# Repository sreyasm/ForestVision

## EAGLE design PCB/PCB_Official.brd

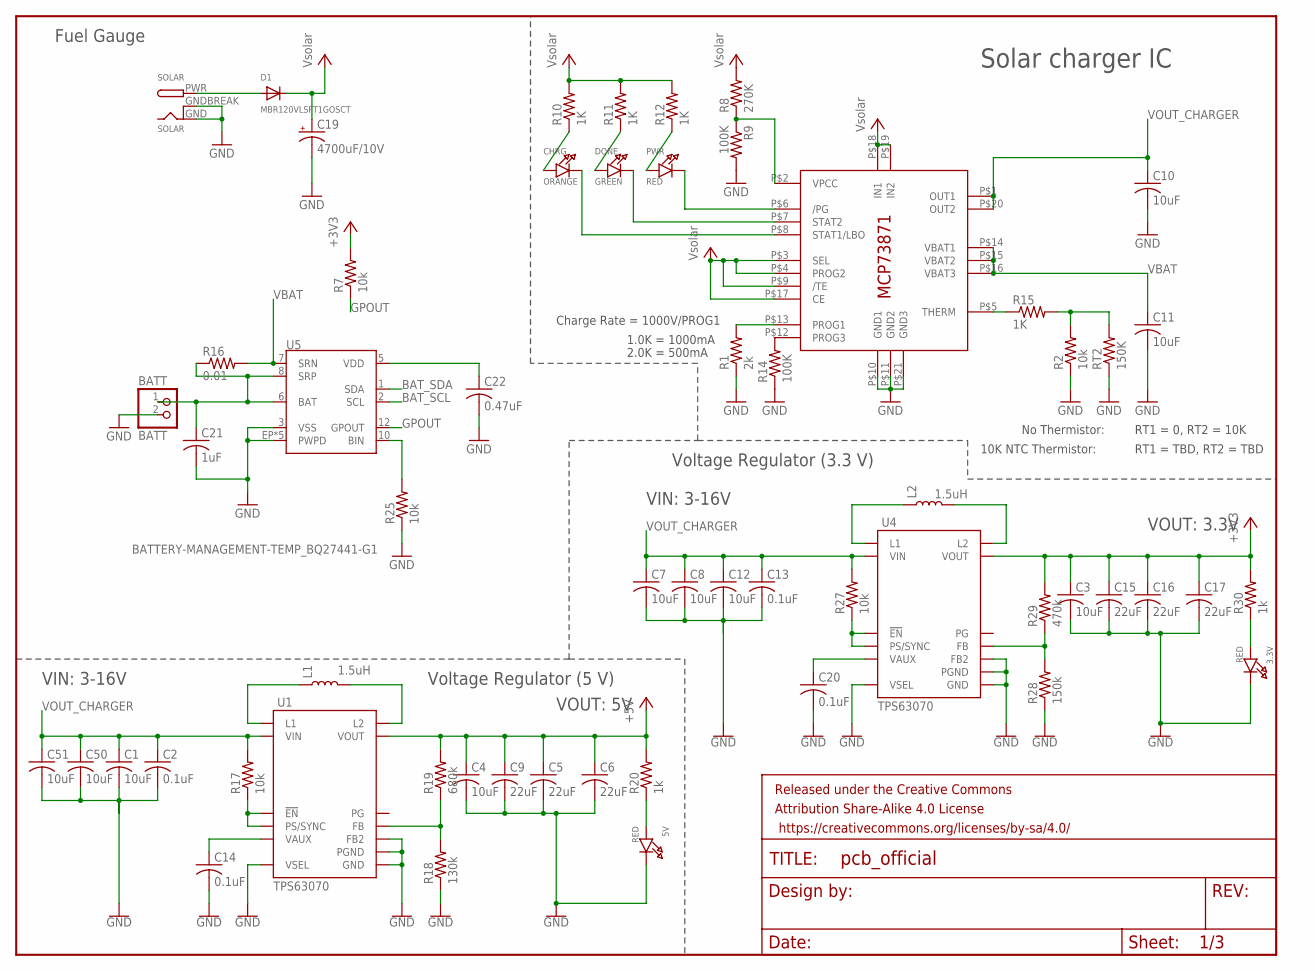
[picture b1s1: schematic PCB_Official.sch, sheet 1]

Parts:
3.3V, 5V: RED; CHIPLED_0805_NOOUTLINE
BATT: BATT; JST-PH-2-SMT-RA
C1, C8, C12, C50: 10uF; C0805
C2, C13: 0.1uF; C0805
C3, C4, C7, C51: 10uF; C0603
C5, C6, C9, C15, C16, C17: 22uF; C0805
C10, C11: 10uF; C0805K
C14, C20: 0.1uF; C0603
C19: 4700uF/10V; ADAFRUIT_E5-13
C21: 1uF; C0805
C22: 0.47uF; C0805
CHRG: ORANGE; CHIPLED_0805_NOOUTLINE
D1: MBR120VLSFT1GOSCT; MICROBUILDER_SOD-123
DONE: GREEN; CHIPLED_0805_NOOUTLINE
FRAME2: FRAME-LETTERNO_PACKAGE; DUMMY
IC1: MCP73871; QFN20_4MM
L1, L2: 1.5uH; XFL4020
PWR: RED; CHIPLED_0805_NOOUTLINE
R1: 2k; R0805
R2, R7, R25: 10k; R0805
R8: 270K; R0805
R9, R14: 100K; R0805
R10, R11, R12: 1K; R0805
R15: 1K; M0805
R16: 0.01; R0805
R17, R27: 10k; R0603
R18: 130k; R0603
R19: 680k; R0603
R20, R30: 1k; R0603
R28: 150k; R0603
R29: 470k; R0603
RT2: 150K; M0805
SOLAR: SOLAR; DCJACK_2MM_PTH
U1, U4: TPS63070; VQFN-15-HR(3X2.5)
U5: BATTERY-MANAGEMENT-TEMP_BQ27441-G1; BATTERY-MANAGEMENT-TEMP_PDSO-N12

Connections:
!EN: R17.1, U1.P$1 (PS/SYNC), U1.P$14 (!EN)
!EN1: R27.1, U4.P$1 (PS/SYNC), U4.P$14 (!EN)
+3V3: C3.1, C15.1, C16.1, C17.1, R7.2, R29.2, R30.2, U4.P$7/8 (VOUT); also elsewhere on the board
+5V: C4.1, C5.1, C6.1, C9.1, R19.2, R20.2, U1.P$7/8 (VOUT); also elsewhere on the board
BAT_SCL: U5.2 (SCL); also elsewhere on the board
BAT_SDA: U5.1 (SDA); also elsewhere on the board
GND: 3.3V.C, 5V.C, BATT.2 (1), C1.2, C2.2, C3.2, C4.2, C5.2, C6.2, C7.2, C8.2, C9.2, C10.2, C11.2, C12.2, C13.2, C14.2, C15.2, C16.2, C17.2, C19.-, C20.2, C21.2, C22.2, C50.2, C51.2, IC1.P$10 (GND1), IC1.P$11 (GND2), IC1.P$21 (GND3), R1.1, R2.1, R9.2, R14.1, R18.1, R25.1, R28.1, RT2.1, SOLAR.GND, SOLAR.GNDBREAK, U1.P$4 (GND), U1.P$6 (FB2), U1.P$10 (PGND), U1.P$15 (VSEL), U4.P$4 (GND), U4.P$6 (FB2), U4.P$10 (PGND), U4.P$15 (VSEL), U5.3 (VSS), U5.EP (PWPD), U5.EP1 (PWPD), U5.EP2 (PWPD), U5.EP3 (PWPD), U5.EP4 (PWPD); also elsewhere on the board
GPOUT: R7.1, U5.12 (GPOUT)
unnamed: L1.P$1 (1), U1.P$11 (L1)
unnamed: L1.P$2 (2), U1.P$9 (L2)
unnamed: IC1.P$2 (VPCC), R8.1, R9.1
unnamed: R18.2, R19.1, U1.P$5 (FB)
unnamed: 5V.A, R20.1
unnamed: C14.1, U1.P$3 (VAUX)
unnamed: L2.P$1 (1), U4.P$11 (L1)
unnamed: L2.P$2 (2), U4.P$9 (L2)
unnamed: C20.1, U4.P$3 (VAUX)
unnamed: IC1.P$6 (/PG), PWR.C
unnamed: DONE.C, IC1.P$7 (STAT2)
unnamed: CHRG.C, IC1.P$8 (STAT1/LBO)
unnamed: CHRG.A, R10.1
unnamed: DONE.A, R11.1
unnamed: PWR.A, R12.1
unnamed: IC1.P$12 (PROG3), R14.2
unnamed: IC1.P$13 (PROG1), R1.2
unnamed: IC1.P$5 (THERM), R15.1
unnamed: R2.2, R15.2, RT2.2
unnamed: 3.3V.A, R30.1
unnamed: R28.2, R29.1, U4.P$5 (FB)
unnamed: BATT.1 (2), C21.1, R16.1, U5.6 (BAT), U5.8 (SRP)
unnamed: C22.1, U5.5 (VDD)
unnamed: R25.2, U5.10 (BIN)
unnamed: D1.A, SOLAR.PWR
VBAT: C11.1, IC1.P$14 (VBAT1), IC1.P$15 (VBAT2), IC1.P$16 (VBAT3), R16.2, U5.7 (SRN)
VCC: C19.+, D1.C, IC1.P$3 (SEL), IC1.P$4 (PROG2), IC1.P$9 (/TE), IC1.P$17 (CE), IC1.P$18 (IN1), IC1.P$19 (IN2), R8.2, R10.2, R11.2, R12.2
VOUT_CHARGER: C1.1, C2.1, C7.1, C8.1, C10.1, C12.1, C13.1, C50.1, C51.1, IC1.P$1 (OUT1), IC1.P$20 (OUT2), R17.2, R27.2, U1.P$12/13 (VIN), U4.P$12/13 (VIN)

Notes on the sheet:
Charge Rate = 1000V/PROG1
1.0K = 1000mA
2.0K = 500mA
No Thermistor:
10K NTC Thermistor:
RT1 = 0, RT2 = 10K
RT1 = TBD, RT2 = TBD
VIN: 3-16V
VOUT: 5V
VOUT: 3.3V
Solar charger IC
Voltage Regulator (3.3 V)
Voltage Regulator (5 V)
Fuel Gauge

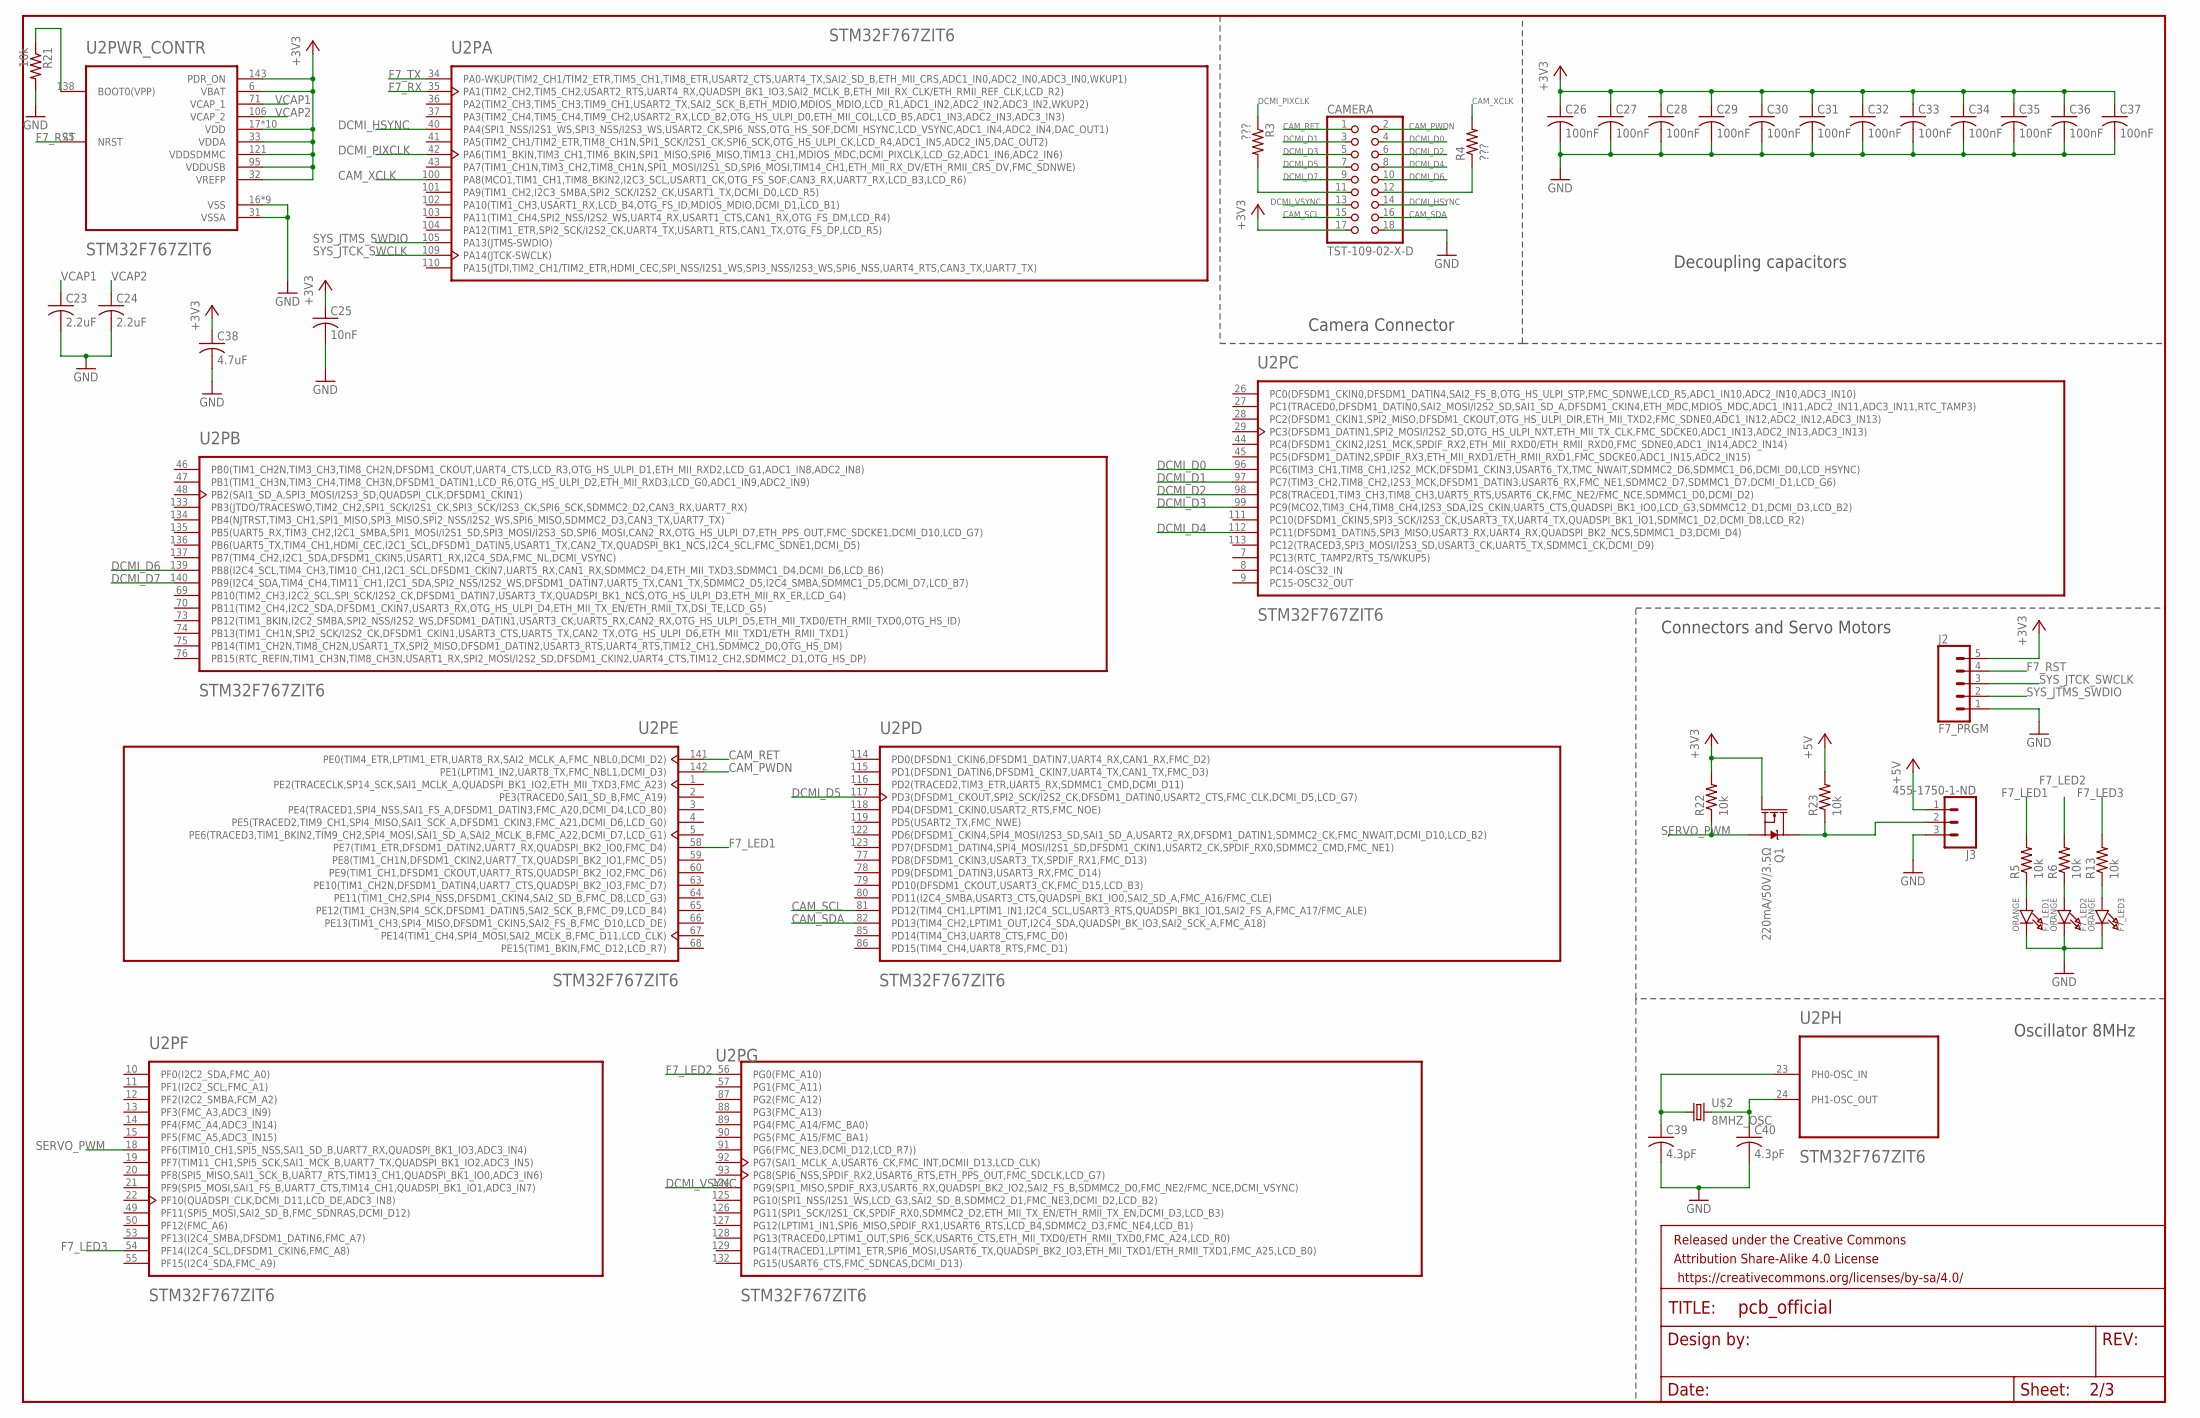
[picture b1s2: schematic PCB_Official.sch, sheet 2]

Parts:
C23, C24: 2.2uF; C0805
C25: 10nF; C0805
C26, C27, C28, C29, C30, C31, C32, C33, C34, C35, C36, C37: 100nF; C0805
C38: 4.7uF; C0805
C39, C40: 4.3pF; C0805
CAMERA: TST-109-02-X-D
F7_LED1, F7_LED2, F7_LED3: ORANGE; CHIPLED_0805_NOOUTLINE
FRAME3: FRAME-LEDGER; CREATIVE_COMMONS
J2: F7_PRGM; 1X05
J3: 455-1750-1-ND; 1X03
Q1: 220mA/50V/3.5Ω; SOT23-3
R3, R4: ???; R0805
R5, R6, R13, R21, R22, R23: 10k; R0805
U2: STM32F767ZIT6; QFP50P2200X2200X160-144N
U$2: 8MHZ_OSC

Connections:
+3V3: C25.1, C26.1, C27.1, C28.1, C29.1, C30.1, C31.1, C32.1, C33.1, C34.1, C35.1, C36.1, C37.1, C38.1, CAMERA.17, J2.5, Q1.1 (G), R22.2, U2.6 (VBAT), U2.17 (VDD), U2.30 (VDD), U2.32 (VREFP), U2.33 (VDDA), U2.39 (VDD), U2.52 (VDD), U2.62 (VDD), U2.72 (VDD), U2.84 (VDD), U2.95 (VDDUSB), U2.108 (VDD), U2.121 (VDDSDMMC), U2.131 (VDD), U2.143 (PDR_ON), U2.144 (VDD); also elsewhere on the board
+5V: J3.1, R23.2; also elsewhere on the board
CAM_PWDN: CAMERA.2, U2.142 (PE1(LPTIM1_IN2,UART8_TX,FMC_NBL1,DCMI_D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)
CAM_RET: CAMERA.1, U2.141 (PE0(TIM4_ETR,LPTIM1_ETR,UART8_RX,SAI2_M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)
CAM_SCL: CAMERA.15, U2.81 (PD12(TIM4_CH1,LPTIM1_IN1,I2C4_SCL,USART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)
CAM_SDA: CAMERA.16, U2.82 (PD13(TIM4_CH2,LPTIM1_OUT,I2C4_SDA,QUADS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)
CAM_XCLK: R4.2, U2.100 (PA8(MCO1,TIM1_CH1,TIM8_BKIN2,I2C3_SCL,U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)
DCMI_D0: CAMERA.4, U2.96 (PC6(TIM3_CH1,TIM8_CH1,I2S2_MCK,DFSDM1_C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)
DCMI_D1: CAMERA.3, U2.97 (PC7(TIM3_CH2,TIM8_CH2,I2S3_MCK,DFSDM1_D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)
DCMI_D2: CAMERA.6, U2.98 (PC8(TRACED1,TIM3_CH3,TIM8_CH3,UART5_RTS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)
DCMI_D3: CAMERA.5, U2.99 (PC9(MCO2,TIM3_CH4,TIM8_CH4,I2S3_SDA,I2S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)
DCMI_D4: CAMERA.8, U2.112 (PC11(DFSDM1_DATIN5,SPI3_MISO,USART3_RX,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)
DCMI_D5: CAMERA.7, U2.117 (PD3(DFSDM1_CKOUT,SPI2_SCK/I2S2_CK,DFSDM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)
DCMI_D6: CAMERA.10, U2.139 (PB8(I2C4_SCL,TIM4_CH3,TIM10_CH1,I2C1_SC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)
DCMI_D7: CAMERA.9, U2.140 (PB9(I2C4_SDA,TIM4_CH4,TIM11_CH1,I2C1_SD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)
DCMI_HSYNC: CAMERA.14, U2.40 (PA4(SPI1_NSS/I2S1_WS,SPI3_NSS/I2S3_WS,U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)
DCMI_PIXCLK: R3.1, U2.42 (PA6(TIM1_BKIN,TIM3_CH1,TIM6_BKIN,SPI1_M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)
DCMI_VSYNC: CAMERA.13, U2.124 (PG9(SPI1_MISO,SPDIF_RX3,USART6_RX,QUADS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)
F7_LED1: R5.2, U2.58 (PE7(TIM1_ETR,DFSDM1_DATIN2,UART7_RX,QUA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)
F7_LED2: R6.2, U2.56 (PG0(FMC_A10))
F7_LED3: R13.2, U2.54 (PF14(I2C4_SCL,DFSDM1_CKIN6,FMC_A8))
F7_RST: J2.4, U2.25 (NRST)
F7_RX: U2.35 (PA1(TIM2_CH2,TIM5_CH2,USART2_RTS,UART4_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); also elsewhere on the board
F7_TX: U2.34 (PA0-WKUP(TIM2_CH1/TIM2_ETR,TIM5_CH1,TIM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); also elsewhere on the board
GND: C23.2, C24.2, C25.2, C26.2, C27.2, C28.2, C29.2, C30.2, C31.2, C32.2, C33.2, C34.2, C35.2, C36.2, C37.2, C38.2, C39.2, C40.2, CAMERA.18, F7_LED1.C, F7_LED2.C, F7_LED3.C, J2.1, J3.3, R21.2, U2.16 (VSS), U2.31 (VSSA), U2.38 (VSS), U2.51 (VSS), U2.61 (VSS), U2.83 (VSS), U2.94 (VSS), U2.107 (VSS), U2.120 (VSS), U2.130 (VSS); also elsewhere on the board
unnamed: R21.1, U2.138 (BOOT0(VPP))
unnamed: C40.1, U2.24 (PH1-OSC_OUT), U$2.P$2 (2)
unnamed: C39.1, U2.23 (PH0-OSC_IN), U$2.P$1 (1)
unnamed: J3.2, Q1.3 (D), R23.1
unnamed: CAMERA.11, R3.2
unnamed: CAMERA.12, R4.1
unnamed: F7_LED2.A, R6.1
unnamed: F7_LED3.A, R13.1
unnamed: F7_LED1.A, R5.1
SERVO_PWM: Q1.2 (S), R22.1, U2.18 (PF6(TIM10_CH1,SPI5_NSS,SAI1_SD_B,UART7_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)
SYS_JTCK_SWCLK: J2.3, U2.109 (PA14(JTCK-SWCLK))
SYS_JTMS_SWDIO: J2.2, U2.105 (PA13(JTMS-SWDIO))
VCAP1: C23.1, U2.71 (VCAP_1)
VCAP2: C24.1, U2.106 (VCAP_2)

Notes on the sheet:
Decoupling capacitors
Camera Connector
Connectors and Servo Motors
Oscillator 8MHz

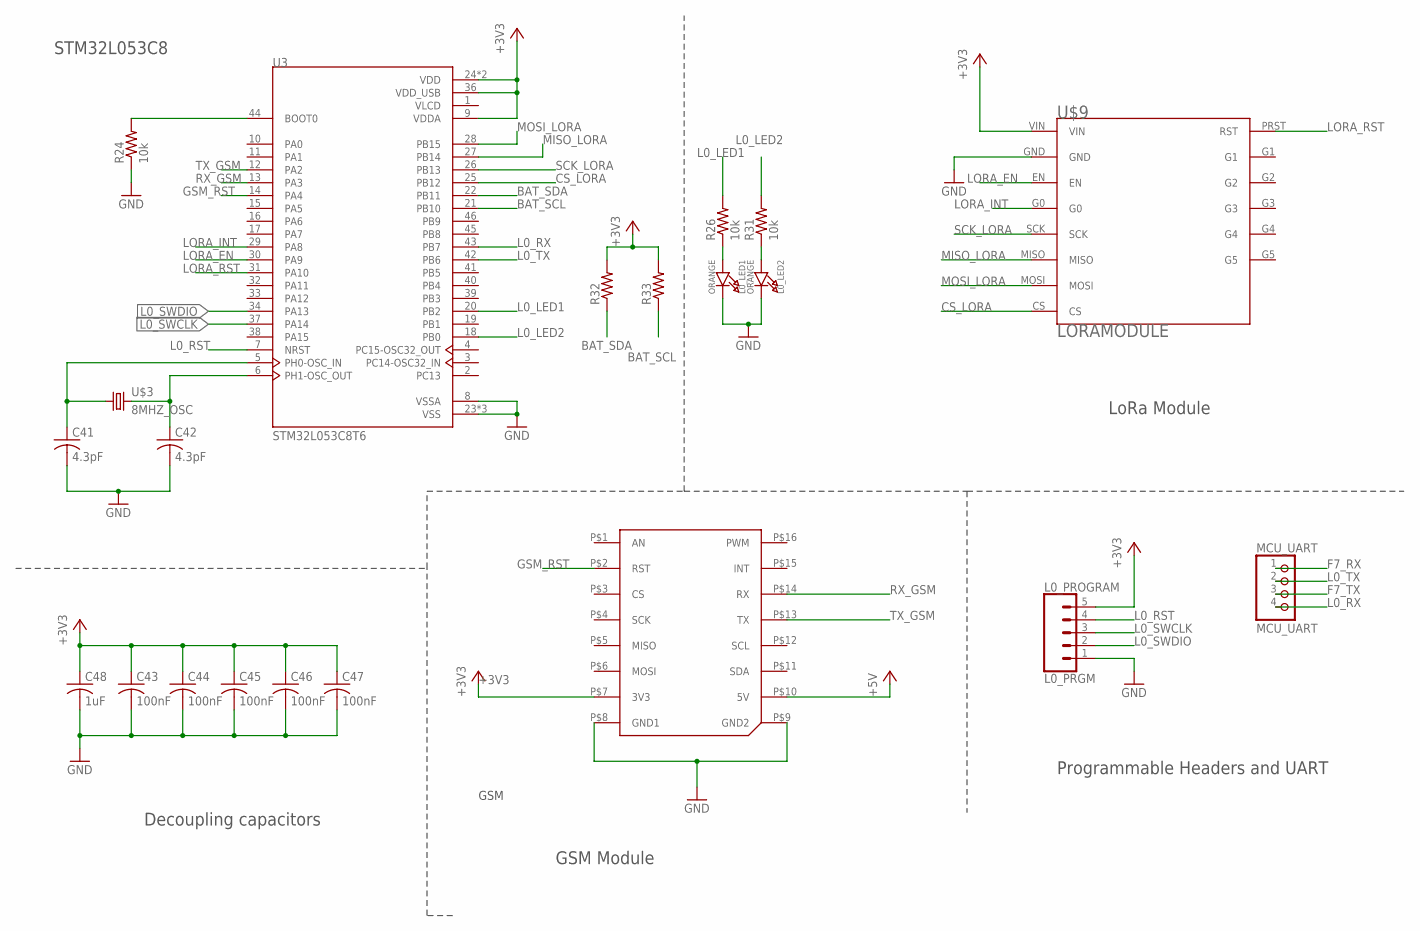
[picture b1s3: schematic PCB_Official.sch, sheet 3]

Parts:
C41, C42: 4.3pF; C0805
C43, C44, C45, C46, C47: 100nF; C0805
C48: 1uF; C0805
L0_LED1, L0_LED2: ORANGE; CHIPLED_0805_NOOUTLINE
L0_PROGRAM: L0_PRGM; 1X05
MCU_UART: MCU_UART; 1X04
R24, R26, R31: 10k; R0805
R32, R33: R-US_R0805; R0805
U3: STM32L053C8T6; QFP50P900X900X160-48N
U$1: MIKROE_CLICKLARGE; MIKROE_BUS_LARGE
U$3: 8MHZ_OSC
U$9: LORAMODULE

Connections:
+3V3: C43.1, C44.1, C45.1, C46.1, C47.1, C48.1, L0_PROGRAM.5, R32.2, R33.2, U3.9 (VDDA), U3.24 (VDD), U3.36 (VDD_USB), U3.48 (VDD), U$1.P$7 (3V3), U$9.VIN; also elsewhere on the board
+5V: U$1.P$10 (5V); also elsewhere on the board
BAT_SCL: R33.1, U3.21 (PB10); also elsewhere on the board
BAT_SDA: R32.1, U3.22 (PB11); also elsewhere on the board
CS_LORA: U3.25 (PB12), U$9.CS
F7_RX: MCU_UART.1; also elsewhere on the board
F7_TX: MCU_UART.3; also elsewhere on the board
GND: C41.2, C42.2, C43.2, C44.2, C45.2, C46.2, C47.2, C48.2, L0_LED1.C, L0_LED2.C, L0_PROGRAM.1, R24.1, U3.8 (VSSA), U3.23 (VSS), U3.35 (VSS), U3.47 (VSS), U$1.P$8 (GND1), U$1.P$9 (GND2), U$9.GND; also elsewhere on the board
GSM_RST: U3.14 (PA4), U$1.P$2 (RST)
L0_LED1: R26.2, U3.20 (PB2)
L0_LED2: R31.2, U3.18 (PB0)
L0_RST: L0_PROGRAM.4, U3.7 (NRST)
L0_RX: MCU_UART.4, U3.43 (PB7)
L0_SWCLK: L0_PROGRAM.3, U3.37 (PA14)
L0_SWDIO: L0_PROGRAM.2, U3.34 (PA13)
L0_TX: MCU_UART.2, U3.42 (PB6)
LORA_EN: U3.30 (PA9), U$9.EN
LORA_INT: U3.29 (PA8), U$9.G0
LORA_RST: U3.31 (PA10), U$9.PRST (RST)
MISO_LORA: U3.27 (PB14), U$9.MISO
MOSI_LORA: U3.28 (PB15), U$9.MOSI
unnamed: R24.2, U3.44 (BOOT0)
unnamed: C42.1, U3.6 (PH1-OSC_OUT), U$3.P$2 (2)
unnamed: C41.1, U3.5 (PH0-OSC_IN), U$3.P$1 (1)
unnamed: L0_LED2.A, R31.1
unnamed: L0_LED1.A, R26.1
RX_GSM: U3.13 (PA3), U$1.P$14 (RX)
SCK_LORA: U3.26 (PB13), U$9.SCK
TX_GSM: U3.12 (PA2), U$1.P$13 (TX)

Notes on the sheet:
GSM
Decoupling capacitors
LoRa Module
GSM Module
Programmable Headers and UART
STM32L053C8

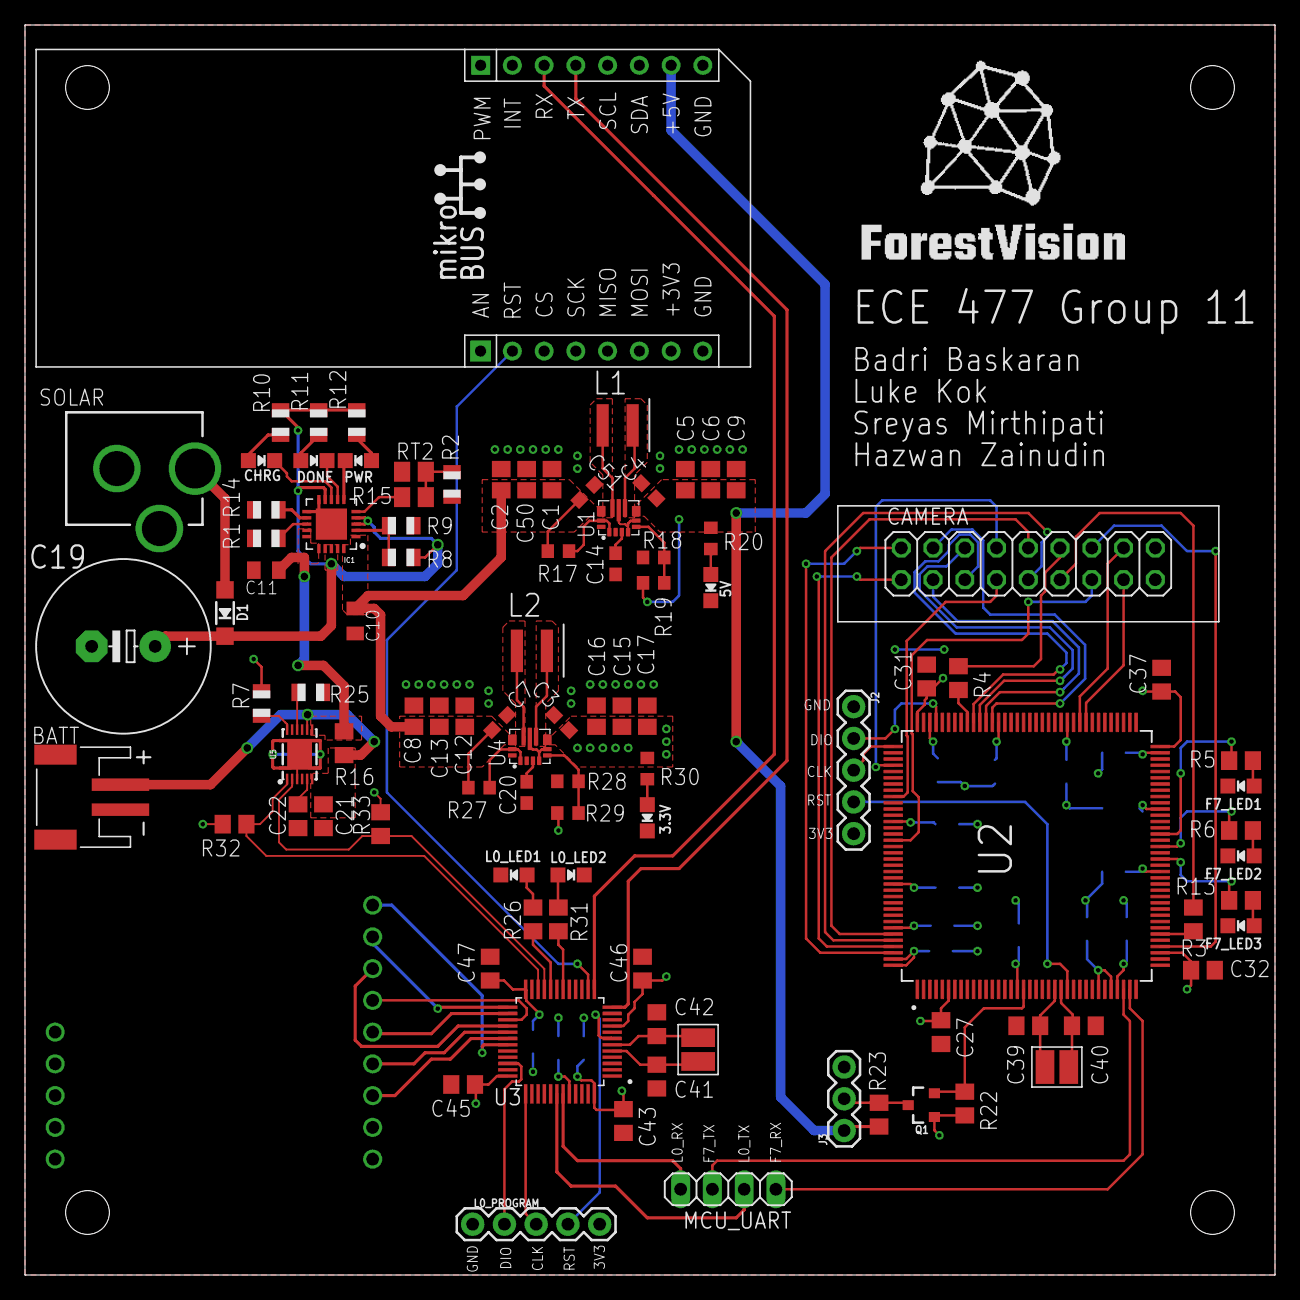
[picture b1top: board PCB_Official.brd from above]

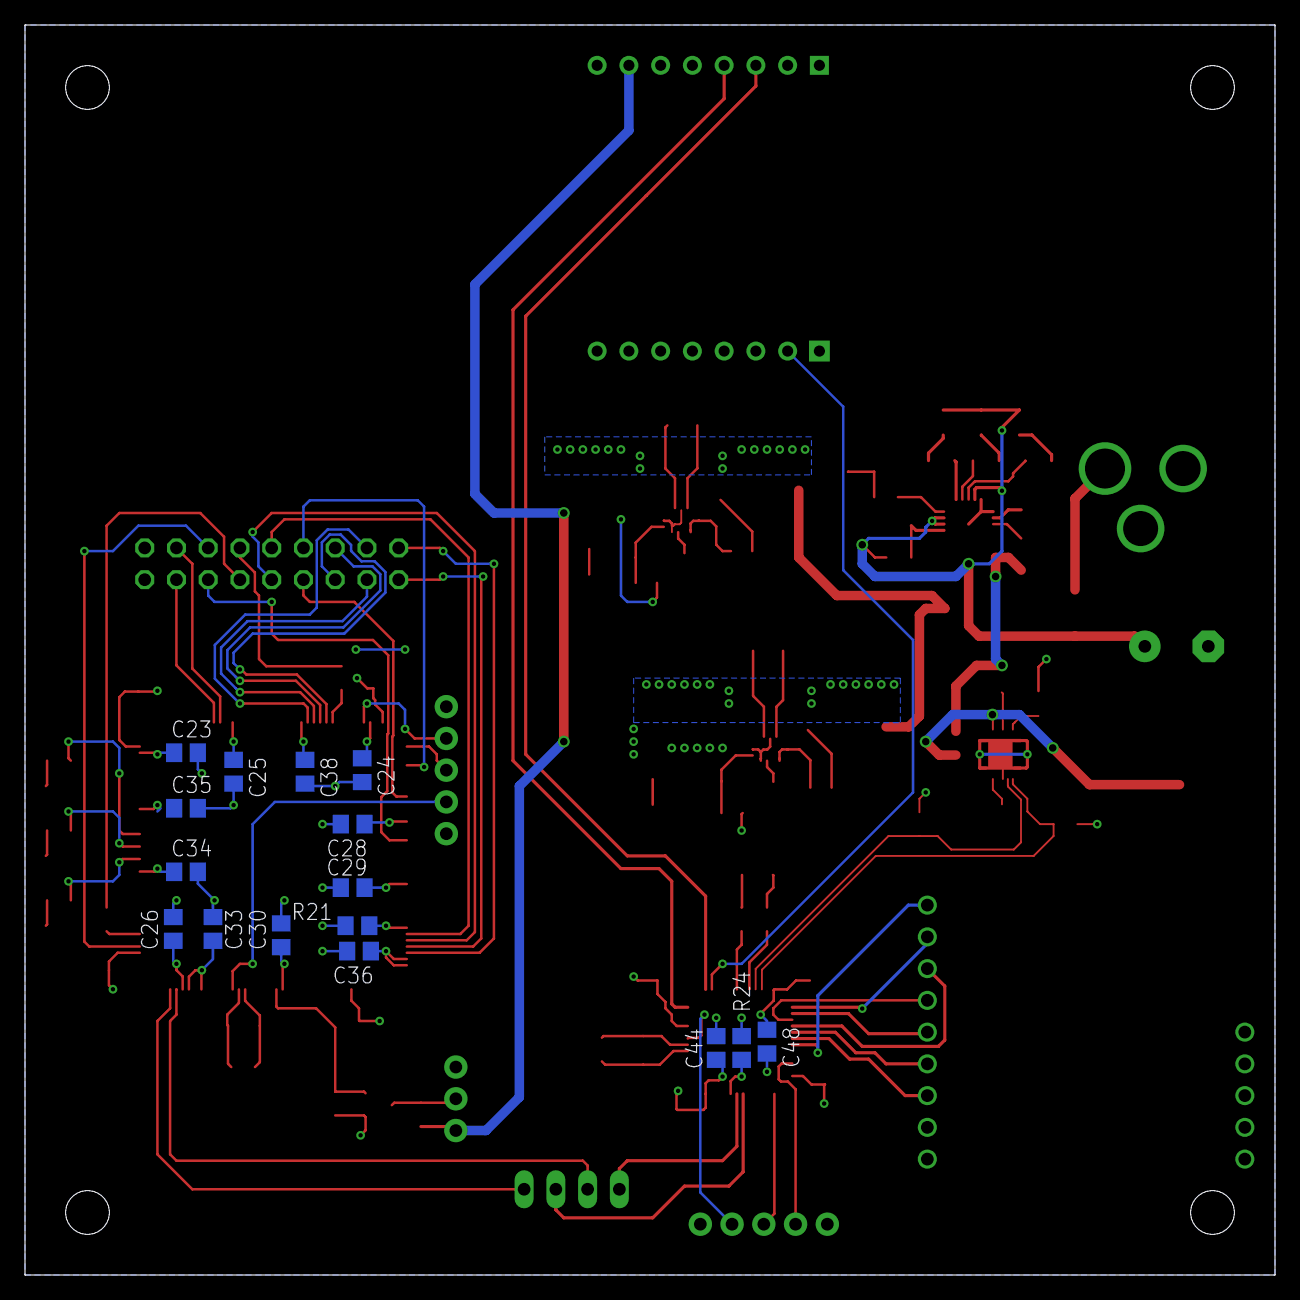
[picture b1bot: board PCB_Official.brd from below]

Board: 2 copper layers, 100.0 x 100.0 mm, 116 parts (16 on the bottom side), 94 nets.

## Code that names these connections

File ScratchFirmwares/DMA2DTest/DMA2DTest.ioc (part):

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Mcu.Name=STM32F767ZITx
Mcu.Package=LQFP144
Mcu.UserName=STM32F767ZITx
PA0/WKUP.Mode=Asynchronous
PA0/WKUP.Signal=UART4_TX
PA1.Mode=Asynchronous
PA1.Signal=UART4_RX
PA13.Mode=Serial_Wire
PA13.Signal=SYS_JTMS-SWDIO
PA14.Mode=Serial_Wire
PA14.Signal=SYS_JTCK-SWCLK
PA4.GPIOParameters=GPIO_Speed,GPIO_PuPd
PA4.GPIO_PuPd=GPIO_PULLUP
PA4.GPIO_Speed=GPIO_SPEED_FREQ_HIGH
PA4.Mode=Slave_8_bits_External_Synchro
PA4.Signal=DCMI_HSYNC
PA6.GPIOParameters=GPIO_Speed,GPIO_PuPd
PA6.GPIO_PuPd=GPIO_PULLUP
PA6.GPIO_Speed=GPIO_SPEED_FREQ_HIGH
PA6.Mode=Slave_8_bits_External_Synchro
PA6.Signal=DCMI_PIXCLK
PA8.GPIOParameters=GPIO_Speed
PA8.GPIO_Speed=GPIO_SPEED_FREQ_VERY_HIGH
PA8.Mode=Clock-out-1
PA8.Signal=RCC_MCO_1
PB8.GPIOParameters=GPIO_Speed,GPIO_PuPd
PB8.GPIO_PuPd=GPIO_PULLUP
PB8.GPIO_Speed=GPIO_SPEED_FREQ_HIGH
PB8.Mode=Slave_8_bits_External_Synchro
PB8.Signal=DCMI_D6
PB9.GPIOParameters=GPIO_Speed,GPIO_PuPd
PB9.GPIO_PuPd=GPIO_PULLUP
PB9.GPIO_Speed=GPIO_SPEED_FREQ_HIGH
PB9.Mode=Slave_8_bits_External_Synchro
PB9.Signal=DCMI_D7
PC11.GPIOParameters=GPIO_Speed,GPIO_PuPd
PC11.GPIO_PuPd=GPIO_PULLUP
PC11.GPIO_Speed=GPIO_SPEED_FREQ_HIGH
PC11.Mode=Slave_8_bits_External_Synchro
PC11.Signal=DCMI_D4
PC6.GPIOParameters=GPIO_Speed,GPIO_PuPd
PC6.GPIO_PuPd=GPIO_PULLUP
PC6.GPIO_Speed=GPIO_SPEED_FREQ_HIGH
PC6.Mode=Slave_8_bits_External_Synchro
PC6.Signal=DCMI_D0
PC7.GPIOParameters=GPIO_Speed,GPIO_PuPd
PC7.GPIO_PuPd=GPIO_PULLUP
PC7.GPIO_Speed=GPIO_SPEED_FREQ_HIGH
PC7.Mode=Slave_8_bits_External_Synchro
PC7.Signal=DCMI_D1
PC8.GPIOParameters=GPIO_Speed,GPIO_PuPd
PC8.GPIO_PuPd=GPIO_PULLUP
PC8.GPIO_Speed=GPIO_SPEED_FREQ_HIGH
PC8.Mode=Slave_8_bits_External_Synchro
PC8.Signal=DCMI_D2
PC9.GPIOParameters=GPIO_Speed,GPIO_PuPd
PC9.GPIO_PuPd=GPIO_PULLUP
PC9.GPIO_Speed=GPIO_SPEED_FREQ_HIGH
PC9.Mode=Slave_8_bits_External_Synchro
PC9.Signal=DCMI_D3
PD12.GPIOParameters=GPIO_PuPdOD
PD12.GPIO_PuPdOD=GPIO_NOPULL
PD12.Mode=I2C
PD12.Signal=I2C4_SCL
PD13.GPIOParameters=GPIO_PuPdOD
PD13.GPIO_PuPdOD=GPIO_NOPULL
PD13.Mode=I2C
PD13.Signal=I2C4_SDA
PD3.GPIOParameters=GPIO_Speed,GPIO_PuPd
PD3.GPIO_PuPd=GPIO_PULLUP
PD3.GPIO_Speed=GPIO_SPEED_FREQ_HIGH
PD3.Mode=Slave_8_bits_External_Synchro
PD3.Signal=DCMI_D5
PE0.GPIOParameters=GPIO_Label
PE0.GPIO_Label=CAM_RET
PE0.Signal=GPIO_Output
PE1.GPIOParameters=GPIO_Label
PE1.GPIO_Label=CAM_PWDN
PE1.Signal=GPIO_Output
PE7.GPIOParameters=GPIO_Label
PE7.GPIO_Label=LED1
PE7.Signal=GPIO_Output
PF14.GPIOParameters=GPIO_Label
PF14.GPIO_Label=LED3
PF14.Signal=GPIO_Output
PF6.Signal=S_TIM10_CH1
PG0.GPIOParameters=GPIO_Label
PG0.GPIO_Label=LED2
PG0.Signal=GPIO_Output
PG9.GPIOParameters=GPIO_Speed,GPIO_PuPd
PG9.GPIO_PuPd=GPIO_PULLUP
PG9.GPIO_Speed=GPIO_SPEED_FREQ_HIGH
PG9.Mode=Slave_8_bits_External_Synchro
PG9.Signal=DCMI_VSYNC
RCC.HSE_VALUE=25000000
RCC.SYSCLKFreq_VALUE=216000000
RCC.SYSCLKSource=RCC_SYSCLKSOURCE_PLLCLK
board=custom

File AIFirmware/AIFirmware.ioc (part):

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Mcu.Name=STM32F767ZITx
Mcu.Package=LQFP144
Mcu.UserName=STM32F767ZITx
PA13.Mode=Serial_Wire
PA13.Signal=SYS_JTMS-SWDIO
PA14.Mode=Serial_Wire
PA14.Signal=SYS_JTCK-SWCLK
PA4.Mode=Slave_8_bits_External_Synchro
PA4.Signal=DCMI_HSYNC
PA6.Mode=Slave_8_bits_External_Synchro
PA6.Signal=DCMI_PIXCLK
PA8.Mode=Clock-out-1
PA8.Signal=RCC_MCO_1
PB7.GPIOParameters=GPIO_Label
PB7.GPIO_Label=LED_BLUE
PB7.Signal=GPIO_Output
PB8.Mode=Slave_8_bits_External_Synchro
PB8.Signal=DCMI_D6
PB9.Mode=Slave_8_bits_External_Synchro
PB9.Signal=DCMI_D7
PC11.Mode=Slave_8_bits_External_Synchro
PC11.Signal=DCMI_D4
PC6.Mode=Slave_8_bits_External_Synchro
PC6.Signal=DCMI_D0
PC7.Mode=Slave_8_bits_External_Synchro
PC7.Signal=DCMI_D1
PC8.Mode=Slave_8_bits_External_Synchro
PC8.Signal=DCMI_D2
PC9.Mode=Slave_8_bits_External_Synchro
PC9.Signal=DCMI_D3
PD12.Mode=I2C
PD12.Signal=I2C4_SCL
PD13.Mode=I2C
PD13.Signal=I2C4_SDA
PD3.Mode=Slave_8_bits_External_Synchro
PD3.Signal=DCMI_D5
PE0.Signal=GPIO_Output
PE1.Signal=GPIO_Output
PE7.Signal=GPIO_Output
PF14.Signal=GPIO_Output
PF6.Signal=S_TIM10_CH1
PG0.Signal=GPIO_Output
PG9.Mode=Slave_8_bits_External_Synchro
PG9.Signal=DCMI_VSYNC
PH0/OSC_IN.Mode=HSE-External-Clock-Source
PH0/OSC_IN.Signal=RCC_OSC_IN
PH1/OSC_OUT.Mode=HSE-External-Clock-Source
PH1/OSC_OUT.Signal=RCC_OSC_OUT
RCC.HSE_VALUE=8000000
RCC.SYSCLKFreq_VALUE=216000000
RCC.SYSCLKSource=RCC_SYSCLKSOURCE_PLLCLK
board=custom

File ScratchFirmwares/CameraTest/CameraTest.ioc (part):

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Mcu.Name=STM32F767ZITx
Mcu.Package=LQFP144
Mcu.UserName=STM32F767ZITx
PA1.GPIOParameters=GPIO_Label
PA1.GPIO_Label=RMII_REF_CLK [LAN8742A-CZ-TR_REFCLK0]
PA1.Mode=RMII
PA1.Signal=ETH_REF_CLK
PA10.GPIOParameters=GPIO_Label
PA10.GPIO_Label=USB_ID
PA10.Signal=USB_OTG_FS_ID
PA11.GPIOParameters=GPIO_Label
PA11.GPIO_Label=USB_DM
PA11.Signal=USB_OTG_FS_DM
PA12.GPIOParameters=GPIO_Label
PA12.GPIO_Label=USB_DP
PA12.Signal=USB_OTG_FS_DP
PA13.GPIOParameters=GPIO_Label
PA13.GPIO_Label=TMS
PA13.Mode=Serial_Wire
PA13.Signal=SYS_JTMS-SWDIO
PA14.GPIOParameters=GPIO_Label
PA14.GPIO_Label=TCK
PA14.Mode=Serial_Wire
PA14.Signal=SYS_JTCK-SWCLK
PA2.GPIOParameters=GPIO_Label
PA2.GPIO_Label=RMII_MDIO [LAN8742A-CZ-TR_MDIO]
PA2.Mode=RMII
PA2.Signal=ETH_MDIO
PA4.GPIOParameters=GPIO_Speed,GPIO_PuPd
PA4.GPIO_PuPd=GPIO_PULLUP
PA4.GPIO_Speed=GPIO_SPEED_FREQ_HIGH
PA4.Mode=Slave_8_bits_External_Synchro
PA4.Signal=DCMI_HSYNC
PA6.GPIOParameters=GPIO_Speed,GPIO_PuPd
PA6.GPIO_PuPd=GPIO_PULLUP
PA6.GPIO_Speed=GPIO_SPEED_FREQ_HIGH
PA6.Mode=Slave_8_bits_External_Synchro
PA6.Signal=DCMI_PIXCLK
PA7.GPIOParameters=GPIO_Label
PA7.GPIO_Label=RMII_CRS_DV [LAN8742A-CZ-TR_CRS_DV]
PA7.Mode=RMII
PA7.Signal=ETH_CRS_DV
PA8.GPIOParameters=GPIO_Speed
PA8.GPIO_Speed=GPIO_SPEED_FREQ_VERY_HIGH
PA8.Mode=Clock-out-1
PA8.Signal=RCC_MCO_1
PA9.GPIOParameters=GPIO_Label
PA9.GPIO_Label=USB_VBUS
PA9.Signal=USB_OTG_FS_VBUS
PB13.GPIOParameters=GPIO_Label
PB13.GPIO_Label=RMII_TXD1 [LAN8742A-CZ-TR_TXD1]
PB13.Mode=RMII
PB13.Signal=ETH_TXD1
PB14.GPIOParameters=GPIO_Label
PB14.GPIO_Label=LD3 [Red]
PB14.Signal=GPIO_Output
PB3.GPIOParameters=GPIO_Label
PB3.GPIO_Label=SWO
PB3.Signal=SYS_JTDO-SWO
PB7.GPIOParameters=GPIO_Label
PB7.GPIO_Label=LD2 [Blue]
PB7.Signal=GPIO_Output
PB8.GPIOParameters=GPIO_Speed,GPIO_PuPdOD
PB8.GPIO_PuPdOD=GPIO_NOPULL
PB8.GPIO_Speed=GPIO_SPEED_FREQ_VERY_HIGH
PB8.Mode=I2C
PB8.Signal=I2C1_SCL
PB9.GPIOParameters=GPIO_Speed,GPIO_PuPdOD
PB9.GPIO_PuPdOD=GPIO_NOPULL
PB9.GPIO_Speed=GPIO_SPEED_FREQ_VERY_HIGH
PB9.Mode=I2C
PB9.Signal=I2C1_SDA
PC1.GPIOParameters=GPIO_Label
PC1.GPIO_Label=RMII_MDC [LAN8742A-CZ-TR_MDC]
PC1.Mode=RMII
PC1.Signal=ETH_MDC
PC13.GPIOParameters=GPIO_Label
PC13.GPIO_Label=USER_Btn [B1]
PC13.Signal=GPXTI13
PC14/OSC32_IN.Mode=LSE-External-Oscillator
PC14/OSC32_IN.Signal=RCC_OSC32_IN
PC15/OSC32_OUT.Mode=LSE-External-Oscillator
PC15/OSC32_OUT.Signal=RCC_OSC32_OUT
PC4.GPIOParameters=GPIO_Label
PC4.GPIO_Label=RMII_RXD0 [LAN8742A-CZ-TR_RXD0]
PC4.Mode=RMII
PC4.Signal=ETH_RXD0
PC5.GPIOParameters=GPIO_Label
PC5.GPIO_Label=RMII_RXD1 [LAN8742A-CZ-TR_RXD1]
PC5.Mode=RMII
PC5.Signal=ETH_RXD1
PC6.GPIOParameters=GPIO_Speed,GPIO_PuPd
PC6.GPIO_PuPd=GPIO_PULLUP
PC6.GPIO_Speed=GPIO_SPEED_FREQ_HIGH
PC6.Mode=Slave_8_bits_External_Synchro
PC6.Signal=DCMI_D0
PC7.GPIOParameters=GPIO_Speed,GPIO_PuPd
PC7.GPIO_PuPd=GPIO_PULLUP
PC7.GPIO_Speed=GPIO_SPEED_FREQ_HIGH
PC7.Mode=Slave_8_bits_External_Synchro
PC7.Signal=DCMI_D1
PC9.GPIOParameters=GPIO_Speed,GPIO_PuPd
PC9.GPIO_PuPd=GPIO_PULLUP
PC9.GPIO_Speed=GPIO_SPEED_FREQ_HIGH
PC9.Mode=Slave_8_bits_External_Synchro
PC9.Signal=DCMI_D3
PD3.GPIOParameters=GPIO_Speed,GPIO_PuPd
PD3.GPIO_PuPd=GPIO_PULLUP
PD3.GPIO_Speed=GPIO_SPEED_FREQ_HIGH
PD3.Mode=Slave_8_bits_External_Synchro
PD3.Signal=DCMI_D5
PD5.Mode=Asynchronous
PD5.Signal=USART2_TX
PD6.Mode=Asynchronous
PD6.Signal=USART2_RX
PD8.GPIOParameters=GPIO_Label
PD8.GPIO_Label=STLK_RX [STM32F103CBT6_PA3]
PD8.Mode=Asynchronous
PD8.Signal=USART3_TX
PD9.GPIOParameters=GPIO_Label
PD9.GPIO_Label=STLK_TX [STM32F103CBT6_PA2]
PD9.Mode=Asynchronous
PD9.Signal=USART3_RX
PE0.GPIOParameters=GPIO_Speed,GPIO_PuPd
PE0.GPIO_PuPd=GPIO_PULLUP
PE0.GPIO_Speed=GPIO_SPEED_FREQ_HIGH
PE0.Mode=Slave_8_bits_External_Synchro
PE0.Signal=DCMI_D2
PE4.GPIOParameters=GPIO_Speed,GPIO_PuPd
PE4.GPIO_PuPd=GPIO_PULLUP
PE4.GPIO_Speed=GPIO_SPEED_FREQ_HIGH
PE4.Mode=Slave_8_bits_External_Synchro
PE4.Signal=DCMI_D4
PE5.GPIOParameters=GPIO_Speed,GPIO_PuPd
PE5.GPIO_PuPd=GPIO_PULLUP
PE5.GPIO_Speed=GPIO_SPEED_FREQ_HIGH
PE5.Mode=Slave_8_bits_External_Synchro
PE5.Signal=DCMI_D6
PE6.GPIOParameters=GPIO_Speed,GPIO_PuPd
PE6.GPIO_PuPd=GPIO_PULLUP
PE6.GPIO_Speed=GPIO_SPEED_FREQ_HIGH
PE6.Mode=Slave_8_bits_External_Synchro
PE6.Signal=DCMI_D7
PF2.Signal=GPIO_Input
PG11.GPIOParameters=GPIO_Label
PG11.GPIO_Label=RMII_TX_EN [LAN8742A-CZ-TR_TXEN]
PG11.Mode=RMII
PG11.Signal=ETH_TX_EN
PG13.GPIOParameters=GPIO_Label
PG13.GPIO_Label=RMII_TXD0 [LAN8742A-CZ-TR_TXD0]
PG13.Mode=RMII
PG13.Signal=ETH_TXD0
PG6.GPIOParameters=GPIO_Label
PG6.GPIO_Label=USB_PowerSwitchOn [STMPS2151STR_EN]
PG6.Signal=GPIO_Output
PG7.GPIOParameters=GPIO_Label
PG7.GPIO_Label=USB_OverCurrent [STMPS2151STR_FAULT]
PG7.Signal=GPIO_Input
PG9.GPIOParameters=GPIO_Speed,GPIO_PuPd
PG9.GPIO_PuPd=GPIO_PULLUP
PG9.GPIO_Speed=GPIO_SPEED_FREQ_HIGH
PG9.Mode=Slave_8_bits_External_Synchro
PG9.Signal=DCMI_VSYNC
PH0/OSC_IN.GPIOParameters=GPIO_Label
PH0/OSC_IN.GPIO_Label=MCO [STM32F103CBT6_PA8]
PH0/OSC_IN.Mode=HSE-External-Clock-Source
PH0/OSC_IN.Signal=RCC_OSC_IN
PH1/OSC_OUT.Mode=HSE-External-Clock-Source
PH1/OSC_OUT.Signal=RCC_OSC_OUT
RCC.HSE_VALUE=8000000
RCC.SYSCLKFreq_VALUE=216000000
RCC.SYSCLKSource=RCC_SYSCLKSOURCE_PLLCLK
RCC.SYSCLKSourceVirtual=RCC_SYSCLKSOURCE_PLLCLK
board=NUCLEO-F767ZI
boardIOC=true

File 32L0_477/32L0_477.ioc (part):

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Mcu.Name=STM32L053C(6-8)Tx
Mcu.Package=LQFP48
Mcu.UserName=STM32L053C8Tx
PA10.GPIOParameters=GPIO_Label
PA10.GPIO_Label=LORA_RST
PA10.Signal=GPIO_Output
PA13.GPIOParameters=GPIO_Label
PA13.GPIO_Label=SWDIO
PA13.Mode=Serial_Wire
PA13.Signal=SYS_SWDIO
PA14.GPIOParameters=GPIO_Label
PA14.GPIO_Label=SWCLK
PA14.Mode=Serial_Wire
PA14.Signal=SYS_SWCLK
PA2.GPIOParameters=GPIO_Label
PA2.GPIO_Label=GSM_TX
PA2.Mode=Asynchronous
PA2.Signal=USART2_TX
PA3.GPIOParameters=GPIO_Label
PA3.GPIO_Label=GSM_RX
PA3.Mode=Asynchronous
PA3.Signal=USART2_RX
PA4.GPIOParameters=GPIO_Label
PA4.GPIO_Label=GSM_RST
PA4.Signal=GPIO_Output
PA5.GPIOParameters=GPIO_Label
PA5.GPIO_Label=DEVLED_R
PA5.Signal=GPIO_Output
PA8.GPIOParameters=GPIO_Label
PA8.GPIO_Label=LORA_INT
PA8.Signal=GPXTI8
PA9.GPIOParameters=GPIO_Label
PA9.GPIO_Label=LORA_EN
PA9.Signal=GPIO_Output
PB0.GPIOParameters=GPIO_Label
PB0.GPIO_Label=LED2
PB0.Signal=GPIO_Output
PB10.GPIOParameters=GPIO_Label
PB10.GPIO_Label=BAT_SCL
PB10.Mode=I2C
PB10.Signal=I2C2_SCL
PB11.GPIOParameters=GPIO_Label
PB11.GPIO_Label=BAT_SDA
PB11.Mode=I2C
PB11.Signal=I2C2_SDA
PB12.GPIOParameters=GPIO_Label
PB12.GPIO_Label=LORA_NSS
PB12.Signal=GPIO_Output
PB13.GPIOParameters=GPIO_Label
PB13.GPIO_Label=LORA_SCK
PB13.Mode=Full_Duplex_Master
PB13.Signal=SPI2_SCK
PB14.GPIOParameters=GPIO_Label
PB14.GPIO_Label=LORA_MISO
PB14.Mode=Full_Duplex_Master
PB14.Signal=SPI2_MISO
PB15.GPIOParameters=GPIO_Label
PB15.GPIO_Label=LORA_MOSI
PB15.Mode=Full_Duplex_Master
PB15.Signal=SPI2_MOSI
PB2.GPIOParameters=GPIO_Label
PB2.GPIO_Label=LED1
PB2.Signal=GPIO_Output
PB4.GPIOParameters=GPIO_Label
PB4.GPIO_Label=DEVLED_G
PB4.Signal=GPIO_Output
PB6.GPIOParameters=GPIO_Label
PB6.GPIO_Label=L0_TX
PB6.Mode=Asynchronous
PB6.Signal=USART1_TX
PB7.GPIOParameters=GPIO_Label
PB7.GPIO_Label=L0_RX
PB7.Mode=Asynchronous
PB7.Signal=USART1_RX
RCC.HSE_VALUE=8000000
RCC.SYSCLKFreq_VALUE=32000000
RCC.SYSCLKSource=RCC_SYSCLKSOURCE_PLLCLK
board=STM32L0538-DISCO
boardIOC=true

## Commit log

2019-09-03 Initial commit with README.
2019-09-03 Adding CamTest initial code
2019-09-18 Added cat and dog classifier to AI scratch area.
2019-09-25 Initial commit for website
2019-10-02 Almost complete schematic and board placement
2019-10-05 Schematic almost finalized
2019-10-09 Pre-midpoint design review.
2019-10-15 Major revision after design review
2019-10-15 Camera test is configuring camera
2019-10-15 Added AIFirmware project
2019-10-15 LoRa
2019-10-16 Basic camera frame capture into RAM
2019-10-16 Tables with timers (no database)
2019-10-16 Tables with database
2019-10-16 Shuffled pin assignments for AI MCU
2019-10-17 Added PCB pin assignments and routed camera connector.
2019-10-18 Corrected layout of 5V regulator, WIP for 3.3V regulator. Improved microcontroller layouts as well.
2019-10-18 Passing DRU, need to fix silkscreen
2019-10-19 Submitted PCB for production.
2019-10-29 GSM can send text, needs cleanup
2019-11-02 Added comments and cleaned up the functions a bit. More cleanups will be required later.
2019-11-03 Created L0 blink program for PCB. Able to send image via UART. Image is not clear.
2019-11-04 Image is finally showing up
2019-11-04 Deleted unused camera configs
2019-11-08 Cleaned up a little
2019-11-08 Working RGB565 serial transfer from PCB, need to scale to 100x100
2019-11-10 Initial commit for Fuel Gauge programming
2019-11-11 Added functions for initializing the fuel gauge and reading the battery percentage
2019-11-14 PSSC 3, 4, & 5 - Some memory issues
2019-11-14 Working PSSC 3, 4, and 5 demo completed.
2019-11-24 Working 100x100 crop
2019-11-27 Mesh
2019-11-27 Moved stuff from main to text_update
2019-11-29 Mesh w/ battery
2019-12-01 Added GSM_Check_Signal function, removed redundant AT commands
2019-12-03 Cleaned up code
2019-12-03 Redesigned webpage
2019-12-07 Working on final AI Firmware.
2019-12-07 Crop and RGB888 working so far.
2019-12-09 Final
2019-12-09 Deleted all files except for web
2019-12-09 Added requirements.txt
2019-12-09 Firmware with everything except for inference running.
2019-12-11 Got the network to run on STM32.

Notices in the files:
parts and their libraries:
SparkFun-Aesthetics: Licensing: Creative Commons ShareAlike 4.0 International - https://creativecommons.org/licenses/by-sa/4.0
SparkFun-Aesthetics: Released under the Creative Commons Attribution Share-Alike 4.0 License
SparkFun-Aesthetics: https://creativecommons.org/licenses/by-sa/4.0
